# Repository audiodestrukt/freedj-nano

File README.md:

# freedj-nano

A DJ deck for the smallest ESP32s: **one core, no FPU, no PSRAM** (ESP32-C6 first). The
little sibling of [freedj-esp](../freedj-esp), which needs two cores, an FPU and PSRAM (P4,
S3, A1S). The two repos share the deck's vocabulary (`deck::Event`, the DJ2Go map) but not
the engine: everything here is fixed-point and allocation-free in the audio path.

Status (2026-11-10): **runs and plays audio on the XIAO ESP32C6** through a PCM5102A. It
boots, maps the tracks, and plays, cues and keylocks from the serial console at
5 % of the core. The portable core passes its host tests (keylock pitch, speed and level,
click-free transitions, the UI layouts); the firmware builds for three configs.

Why it's built this way, the measurements and the wrong turns: [docs/DESIGN.md](docs/DESIGN.md).

## What's here

| | |
|---|---|
| **Keylock** (`stretch.cpp`) | WSOLA in fixed point, reading straight from memory-mapped PCM, so no input or overlap buffers: two frames at 50 % overlap, a sin² window whose halves sum to exactly 1, coarse-then-fine AMDF search on mono. About 40 bytes of state. 0.5–2× speed; outside that (and while scratching) it's varispeed |
| **Varispeed** | Linear interpolation at a Q16.16 position: any speed, reverse, scratch crawl |
| **Deck** (`deck.cpp`) | CDJ transport (PLAY, CUE with preview), tempo fader and ranges (±6/10/16/50 %), keylock, jog: nudge while playing, scrub while stopped, scratch while touched. Every jump (cue, load, play, stop, engine switch) is a one-block crossfade, so nothing clicks. Lock-free event queue from the control task, seqlock status for the UI |
| **Tracks** (`library.cpp`, `tools/pack_tracks.py`) | A pack of 16-bit PCM plus 10 ms peak tables, flashed into a partition and memory-mapped: loading a track is pointer arithmetic |
| **MIDI** (`midi.cpp`, `dj2go.cpp`) | Byte-stream parser (running status, real-time, SysEx) for DIN/TRS MIDI on a UART, and freedj-esp's DJ2Go map. The C6 has no USB host: a USB controller needs a USB-to-DIN host box, or BLE-MIDI later |
| **Screens** (`gfx.cpp`, `ui.cpp`) | One small drawing interface, a built-in 5×7 font, three layouts by size: 128×32, 128×64, and color 320×240 / 480×320 with touch buttons and drag-to-scratch on the waveform |
| **Firmware** (`firmware/`) | ESP-IDF 5.5, ESP32-C6: I2S to a PCM5102A, EC11 on PCNT, buttons (GPIO or one-pin resistor ladder), pitch pot, MIDI UART, display backends |

### Displays

| Backend | Panels | How |
|---|---|---|
| `display_u8g2.cpp` | SSD1306 128×64 (0.96"), SH1106 128×64 (1.3"), SSD1306 128×32 (0.91") | [u8g2](https://github.com/olikraus/u8g2) as the controller driver and frame buffer, on I2C. Any other u8g2 panel (SSD1309, ST7567, ...) is one more `Setup` line. u8g2 is only the driver: the UI and font are ours, so it could be swapped out |
| `display_tft.cpp` | ILI9341 320×240 (the 2.8" and 3.2"), ST7796 480×320 (the 4"), FT6336 touch | ESP-IDF `esp_lcd` over SPI, no LVGL. No frame buffer: the screen is drawn in 16-row bands into two DMA buffers, and a band is sent only if it changed (hash per band) |

The ST7796 runs on the ILI9341 driver with its own init sequence, because Espressif's ST7796
component doesn't list the C6 as a target.

## Screens

| 128×64 OLED | 2.8" TFT |
|---|---|
|  |  |

Rendered on the host by the tests (`build/tests/out/*.ppm`), from the same code the firmware runs.

## Boards

Pin maps are in `firmware/main/board.h`. **Not checked on hardware yet.**

**Seeed XIAO ESP32C6, with the 3.2" touch TFT** (`xiao_tft`): runs on the bench at 28.5 fps,
17.6 ms per frame at 40 MHz SPI (the A1S manages 7 fps on the same panel: its screen lines are
shared). The screen takes the encoder's pins, so touch does jog and browse: SCK D8, MOSI D10,
CS D3, DC D9, touch SDA D4 / SCL D5; panel RST, LED and CTP_RST to 3V3, VCC to 5V; I2S BCK D1,
LRCK D2, DIN **D6**; ladder D0; MIDI D7.

**Seeed XIAO ESP32C6 with an OLED** (`xiao_oled`, the default): OLED + encoder:

| Pin | Use |
|---|---|
| D1 / D2 / D10 (GPIO 1 / 2 / 18) | I2S BCK / LRCK / DIN to the PCM5102A |
| D4 / D5 (22 / 23) | I2C SDA / SCL: OLED |
| D8 / D9 / D3 (19 / 20 / 21) | EC11 A / B / push |
| D0 (0, ADC) | 4 buttons on a ladder: 10k to 3V3, then PLAY 0R, CUE 2k2, KEY 4k7, LIST 10k to GND |
| D7 (17) | MIDI in (UART1 RX, via an optocoupler) |
| D6 (16) | spare |

**ESP32-C6-DevKitC-1** (`devkit_tft` for the 2.8"/3.2", `devkit_tft4` for the 4"): TFT SCK 6,
MOSI 7, CS 18, DC 19, RST to 3V3; touch and OLED on I2C 22/23; I2S 10/11/21; EC11 3/5,
push on 9 (the BOOT button); PLAY 0, CUE 1, KEY 2; pitch pot on 4; MIDI in on 20.

**PCM5102A** breakout: SCK to GND (no MCLK: its PLL runs off BCK, which is set to 64 fs),
XSMT high, FMT low. Line out only; a headphone amp is a separate board.

## Controls

| | |
|---|---|
| Encoder | Jog: nudge while playing, scrub while stopped |
| KEY + encoder | Tempo (boards without a pot). KEY tap: keylock |
| Push or LIST | Track list. In the list, the encoder browses and push loads |
| PLAY, CUE | As on a CDJ: CUE while playing returns to the cue and pauses; CUE while paused sets the cue and previews while held; PLAY during a preview keeps playing |
| Touch (TFT) | CUE / PLAY / KEY / LIST buttons; drag the waveform to scratch |
| MIDI | The DJ2Go map: either deck's controls drive the one deck |
| Controller on the computer | freedj-esp's `tools/midi_bridge.py --port /dev/ttyACM0` forwards a USB controller (the DJ2Go) over the serial port: 0x01 + a USB-MIDI packet, decoded with the DJ2Go map |
| Serial console | Over the USB port, for the bench: `p` play, `c` cue (tap), `k` keylock, `+` / `-` tempo 1 %, `0` tempo 0, `r` range, `n` / `b` next / previous track, `j` / `J` jog, `l` list, `?` help. Keys sent while it boots are lost (opening the port resets the C6) |

## Build

```sh
tools/build.sh                          # all firmware configs (Docker, ESP-IDF 5.5) + host tests
tools/build.sh devkit_tft               # one config
cmake -S tests -B build/tests && cmake --build build/tests && (cd build/tests && ./nano_tests)
```

Host tests write listening files (`out/keylock_080.wav`, `keylock_125.wav`, `deck_session.wav`)
and screenshots of every layout.

## Flash

```sh
cd firmware/build_xiao_oled && esptool --chip esp32c6 -b 460800 write-flash @flash_args
tools/pack_tracks.py music/*.mp3 -o tracks.bin     # 22.05 kHz mono; --stereo, --rate 32000
esptool --chip esp32c6 write-flash 0x180000 tracks.bin
```

The `tracks` partition is 2.5 MB on a 4 MB board: about 60 s of 22.05 kHz mono. Fine for
bring-up; storage is the first thing to grow (see the roadmap).

## Budget

| | xiao_oled | devkit_tft |
|---|---|---|
| App image | 269 KB (82 % of the partition free) | 312 KB |
| Static RAM (DIRAM) | 69 KB of 452 KB | 79 KB |
| Audio CPU, 22.05 kHz mono | stopped 0.5 %, playing 1.4 %, **keylock 5.0 %** (XIAO, 160 MHz) | |
| Audio CPU, 44.1 kHz stereo | playing 3.1 %, **keylock 16.4 %, worst block 34 % of its deadline, 0 dropouts** (with the TFT at ~43 fps) | |
| Free heap while playing | 424 KB | |

The firmware prints a budget line every 2 s: audio % of the core (and which engine), UI ms per
frame, free heap.

## Roadmap

1. **Bench bring-up** on the XIAO: audio out, the budget line, encoder and ladder.
2. **More music:** stream from microSD instead of flash (needs a small read-ahead cache for
   the keylock's random access), or IMA ADPCM in the pack (4:1, block-wise so it stays
   seekable).
3. **BLE-MIDI**, since the C6 has no USB host.
4. **New chips** ([docs/TARGETS.md](docs/TARGETS.md)): the **RP2350** as the second real
   target (two cores, memory-mapped flash, PIO I2S, USB host for rekordbox sticks), and the
   **CH32V003** (10 cents, 2 KB RAM, PWM audio) as a how-small-can-it-go experiment
   ([the 10-cent deck plan](docs/DECK10C.md)). First
   step: cross-compile the engine and count cycles per sample.
5. Beetle ESP32-C6 pin map; the C3/H2.

## License

GPL-3.0-or-later, as freedj-esp. `deck_event` and `dj2go` are copied from freedj-esp
(2026-11-08). u8g2 is BSD-2-Clause; the Helvetica bitmap fonts in `fonts.cpp` are Adobe / DEC under the X11
license; the ST7796 init sequence is from Espressif's
esp_lcd_st7796 (Apache-2.0).

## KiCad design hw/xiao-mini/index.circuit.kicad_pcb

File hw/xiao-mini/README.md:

# XIAO mini player (carrier board)

A 72 x 46 mm, 2-layer carrier for a socketed **Seeed XIAO ESP32-C6**. It wires everything the
C6 firmware already expects (`firmware/main/board.h`, `CONFIG_NANO_BOARD_XIAO_C6`, OLED
layout), so it runs today's C6 build unchanged: 16-bit audio through a PCM5102A DAC.

| Block | Parts | XIAO pins |
|---|---|---|
| DAC | PCM5102A (hardware mode: SCK, FMT, FLT, DEMP to GND, XSMT pulled up), 470 R + 2.2 nF out | D1 BCK, D2 WS, D10 DOUT |
| Out | 3.5 mm stereo jack, left edge. **Line level** (into a mixer or powered speakers); the PCM5102A wants >= 1 kOhm, so headphones will be quiet and distort when loud | |
| Screen | 4-pin header for a 0.96" / 1.3" SSD1306/SH1106 I2C module: GND VCC SCL SDA | D4 SDA, D5 SCL |
| Jog / browse | EC11 (Bourns PEC11R) with push, 10k pull-ups | D8 A, D9 B, D3 push |
| Buttons | PLAY, CUE, KEY, LIST on one ADC pin: 10k pull-up, 0 / 2k2 / 4k7 / 10k to GND (the firmware's `LADDER_MV`) | D0 |
| MIDI in | 3-pin header GND RX 3V3, for the bridge's UART | D7 |
| Battery | JST-PH LiPo socket, right edge, plus two pads beside it: wire them to the BAT pads under the XIAO (it has the charger) | |
| Spare | | D6 |

USB-C (the XIAO's) leaves the top edge. Four M2 holes in the corners.

## State

Routed and checked: 0 shorts, 0 open nets, KiCad DRC clean under JLCPCB rules, DFM (hole
spacing, via sizes) clean, no floating pads. `fab/` has Gerbers, drill, CPL and BOMs for JLCPCB
(assembled: DAC, passives, jack, JST, EC11, buttons) and PCBWay. Not built yet.

**Check before ordering:**
- **Jack pinout.** No datasheet drawing for the PJ-325C5-G was found. The board assumes pin 1
  sleeve, 2 tip (L), 3 ring (R) (`JACK_PIN` in `index.circuit.tsx`). Check the part (a
  multimeter on a sample, or the drawing) or swap in a jack you know.
- **OLED header order.** GND VCC SCL SDA is the common one, but some modules are VCC GND.
- **R2 / R3 (470 R)** have no LCSC number yet (in the hand-solder list): pick one at order time.
- **XIAO row spacing** (15.24 mm) and the JST's polarity against your batteries.

## Rebuild

```
npm ci                                   # tscircuit, pinned by package-lock.json
bash scripts/route2.sh                   # export, outline gate, GND pour, route (Freerouting + srj), DRC
bash scripts/make_fab.sh index.circuit.kicad_pcb freedj-nano-xiao-mini both
```

The source of truth is `index.circuit.tsx` (placement in code); `index.circuit.kicad_pcb` is the
routed result. Parts: `imports/` (JLC footprints), `lib/Xiao.tsx` (the socket),
`lib/GndVia.tsx` (stitching vias for the DAC's tie-low pins, as parts so the router keeps them).
Scripts are the pcb-layout skill's.

## Other XIAOs

The S3, C3 and RP2040/RP2350 XIAOs have the same pinout and fit the same socket; the firmware
needs a pin map for each (the S3 one would follow freedj-esp's S3 port).

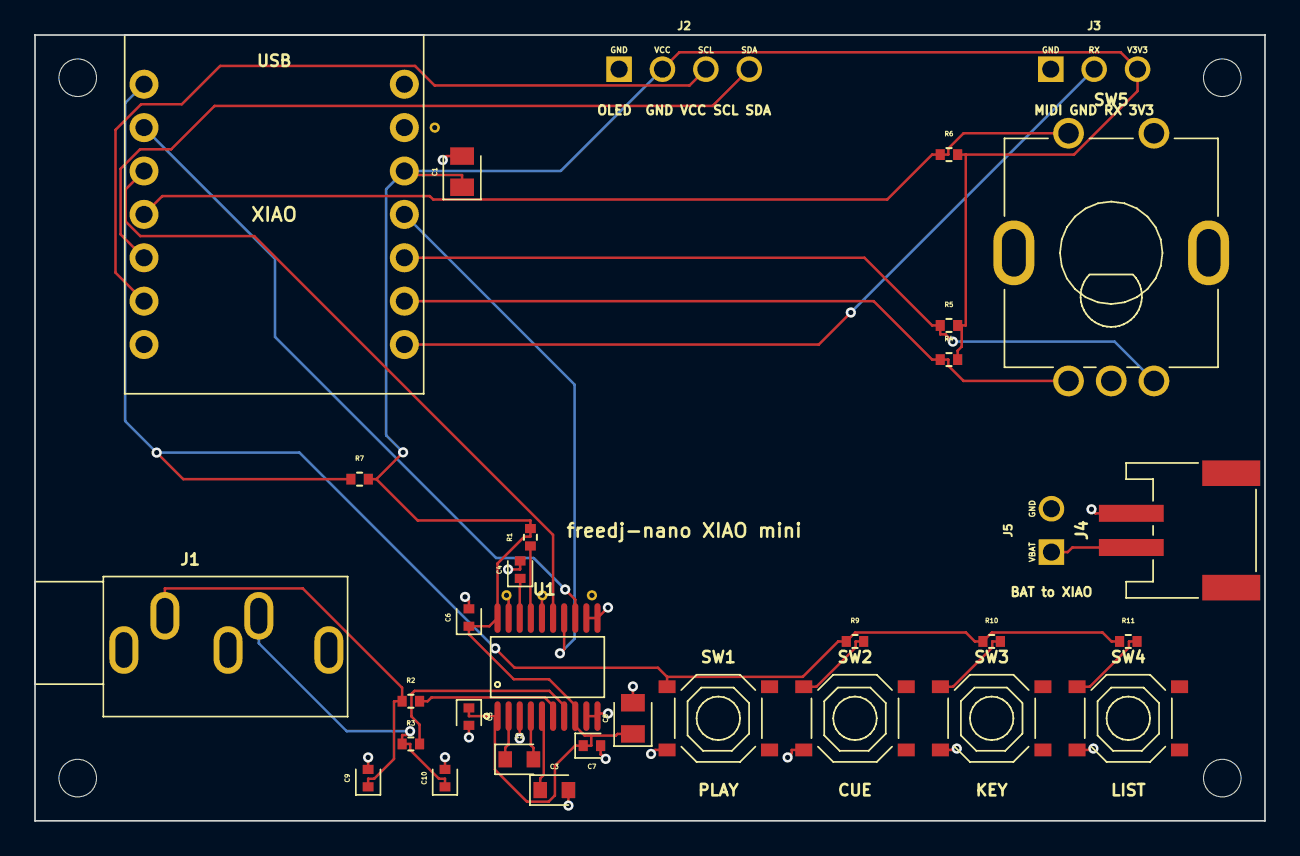
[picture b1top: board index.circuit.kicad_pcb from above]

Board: 2 copper layers, 72.0 x 46.0 mm, 36 parts (0 on the bottom side), 25 nets.

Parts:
C1, C8: 10uF; capacitor_0805
C2, C3: 2.2uF; capacitor_0603
C4: 1uF; capacitor_0402
C5, C6, C7: 100nF; capacitor_0402
C9, C10: 2.2nF; capacitor_0402
J1: PJ_325C5_G
J2: J2; pin_header_pinrow4
J3: J3; pin_header_pinrow3
J4: S2B_PH_SM4_TB_LF__SN_; S2B_PH_SM4_TB_LF_SN
J5: J5; pin_header_pinrow2
R1, R4, R5, R6, R7, R11: 10kΩ; resistor_res0402
R2, R3: 470Ω; resistor_res0402
R9: 2.2kΩ; resistor_res0402
R10: 4.7kΩ; resistor_res0402
SW1, SW2, SW3, SW4: TS_1187A_B_A_B
SW5: PEC11R_4015F_S0024
U1: PCM5102APWR
U2: Seeed_XIAO_socketed
V1, V2, V3, V4: via

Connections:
BCK: U1.13, U2.2
C2.pin1 to U1.CAPP: C2.1, U1.2
C2.pin2 to U1.CAPM: C2.2, U1.4
C3.pin1 to U1.VNEG: C3.1, U1.5
C4.pin1 to U1.LDOO: C4.1, U1.18
DIN: U1.14, U2.11
ENC_A: R4.1, SW5.3, U2.13
ENC_B: R5.1, SW5.5, U2.12
ENC_SW: R6.1, SW5.1, U2.4
GND: C1.2, C3.2, C4.2, C5.2, C6.2, C7.2, C8.2, C9.2, C10.2, J1.1, J2.1, J3.1, J4.2, J5.2, SW1.3, SW2.3, SW3.3, SW4.3, SW5.2, SW5.4, SW5.6, SW5.7, U1.3, U1.9, U1.10, U1.11, U1.12, U1.16, U1.19, U2.9, V1.1, V2.1, V3.1, V4.1
JL: C9.1, J1.2, R2.1
JR: C10.1, J1.3, R3.1
LADDER: R7.1, R9.1, R10.1, R11.1, SW1.1, U2.1
LRCK: U1.15, U2.3
MIDI_RX: J3.2, U2.14
R1.pin1 to U1.XSMT: R1.1, U1.17
R2.pin2 to U1.OUTL: R2.2, U1.6
R3.pin2 to U1.OUTR: R3.2, U1.7
R9.pin2 to SW2.A: R9.2, SW2.1
R10.pin2 to SW3.A: R10.2, SW3.1
R11.pin2 to SW4.A: R11.2, SW4.1
SCL: J2.3, U2.6
SDA: J2.4, U2.5
V3V3: C1.1, C5.1, C6.1, C7.1, C8.1, J2.2, J3.3, R1.2, R4.2, R5.2, R6.2, R7.2, U1.1, U1.8, U1.20, U2.10
VBAT: J4.1, J5.1

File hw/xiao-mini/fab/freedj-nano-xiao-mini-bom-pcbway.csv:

Item#,Designator,Qty,Comment,Footprint,Manufacturer Part Number,Manufacturer,LCSC Part No
1,"C1,C8",2,10uF,capacitor_0805,CL21A106KAYNNNE,Samsung Electro-Mechanics,C15850
2,"C10,C9",2,2.2nF,capacitor_0402,CC0402KRX7R9BB222,YAGEO,C106861
3,"C2,C3",2,2.2uF,capacitor_0603,CL10A225KO8NNNC,Samsung Electro-Mechanics,C23630
4,C4,1,1uF,capacitor_0402,CL05A105KA5NQNC,Samsung Electro-Mechanics,C52923
5,"C5,C6,C7",3,100nF,capacitor_0402,CL05B104KO5NNNC,Samsung Electro-Mechanics,C1525
6,J1,1,PJ_325C5_G,PJ_325C5_G,PJ_325C5_G,,C692438
7,J4,1,S2B_PH_SM4_TB_LF__SN_,S2B_PH_SM4_TB_LF_SN,S2B_PH_SM4_TB_LF__SN_,,C295747
8,R10,1,4.7k,resistor_res0402,ERJ2RKF4701X,Panasonic,C400631
9,"R1,R11,R4,R5,R6,R7",6,10k,resistor_res0402,0402WGF1002TCE,UNI-ROYAL(Uniroyal Elec),C25744
10,R9,1,2.2k,resistor_res0402,0402WGF2201TCE,UNI-ROYAL(Uniroyal Elec),C25879
11,SW5,1,PEC11R_4015F_S0024,PEC11R_4015F_S0024,PEC11R_4015F_S0024,,C143789
12,"SW1,SW2,SW3,SW4",4,TS_1187A_B_A_B,TS_1187A_B_A_B,TS_1187A_B_A_B,,C318884
13,U1,1,PCM5102APWR,PCM5102APWR,PCM5102APWR,,C107671

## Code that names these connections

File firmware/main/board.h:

// SPDX-FileCopyrightText: 2026 Dan Newcome
// SPDX-License-Identifier: GPL-3.0-or-later
#pragma once
// Pin maps. Not checked on hardware yet: confirm against the board's pinout
// before wiring. C6 pins to avoid: 8, 9, 15 (strapping; 9 is BOOT, fine as an
// input after boot), 12/13 (USB), 24-30 (flash).

#include "driver/gpio.h"
#include "sdkconfig.h"

namespace board {

constexpr gpio_num_t NC = GPIO_NUM_NC;

#if CONFIG_NANO_BOARD_XIAO_C6
// Seeed XIAO ESP32C6: D0=0 D1=1 D2=2 D3=21 D4=22 D5=23 D6=16 D7=17 D8=19 D9=20 D10=18.
// Eleven pins, so the four buttons share one ADC pin (resistor ladder). Two layouts:
// an I2C OLED + EC11, or an SPI TFT + touch that takes the encoder's pins (touch
// does jog and browse) and moves I2S DOUT to D6.
constexpr const char* NAME = "XIAO ESP32C6";
constexpr gpio_num_t I2C_SDA = GPIO_NUM_22, I2C_SCL = GPIO_NUM_23;                         // D4, D5: OLED or touch
#if CONFIG_NANO_DISPLAY_TFT
constexpr gpio_num_t I2S_BCK = GPIO_NUM_1,  I2S_WS = GPIO_NUM_2, I2S_DOUT = GPIO_NUM_16;   // D1, D2, D6 -> PCM5102A
constexpr gpio_num_t ENC_A = GPIO_NUM_NC,   ENC_B = GPIO_NUM_NC, ENC_PUSH = GPIO_NUM_NC;
// SCK D8, MOSI D10, CS D3, DC D9. Panel RST, LED and CTP_RST to 3V3; SDO and CTP_INT unused.
constexpr gpio_num_t TFT_SCK = GPIO_NUM_19, TFT_MOSI = GPIO_NUM_18, TFT_CS = GPIO_NUM_21, TFT_DC = GPIO_NUM_20;
constexpr gpio_num_t TFT_RST = GPIO_NUM_NC;
#else
constexpr gpio_num_t I2S_BCK = GPIO_NUM_1,  I2S_WS = GPIO_NUM_2, I2S_DOUT = GPIO_NUM_18;   // D1, D2, D10 -> PCM5102A
constexpr gpio_num_t ENC_A = GPIO_NUM_19,   ENC_B = GPIO_NUM_20, ENC_PUSH = GPIO_NUM_21;   // D8, D9, D3: EC11
constexpr gpio_num_t TFT_SCK = GPIO_NUM_NC, TFT_MOSI = GPIO_NUM_NC, TFT_CS = GPIO_NUM_NC, TFT_DC = GPIO_NUM_NC, TFT_RST = GPIO_NUM_NC;
#endif
constexpr gpio_num_t MIDI_RX = GPIO_NUM_17;                                                 // D7
// Button ladder on D0 (ADC1 ch 0): 10k pull-up to 3V3, each button to GND
// through its resistor. Nominal mV with nothing pressed: 3300.
constexpr gpio_num_t LADDER = GPIO_NUM_0;
constexpr int LADDER_CH = 0;
// PLAY 0R (0 mV), CUE 2k2 (595), KEY 4k7 (1055), LIST 10k (1650)
constexpr int LADDER_MV[4] = {0, 595, 1055, 1650};
constexpr gpio_num_t BTN_PLAY = NC, BTN_CUE = NC, BTN_KEY = NC, BTN_LIST = NC;
constexpr gpio_num_t POT = NC; constexpr int POT_CH = -1;

#elif CONFIG_NANO_BOARD_DEVKIT_C6
// ESP32-C6-DevKitC-1. TFT on the SPI2 IOMUX pins (6, 7) for the full clock.
constexpr const char* NAME = "ESP32-C6-DevKitC-1";
constexpr gpio_num_t I2S_BCK = GPIO_NUM_10, I2S_WS = GPIO_NUM_11, I2S_DOUT = GPIO_NUM_21;
constexpr gpio_num_t I2C_SDA = GPIO_NUM_22, I2C_SCL = GPIO_NUM_23;                         // OLED or touch
constexpr gpio_num_t ENC_A = GPIO_NUM_3,    ENC_B = GPIO_NUM_5,  ENC_PUSH = GPIO_NUM_9;    // push = BOOT button too
constexpr gpio_num_t MIDI_RX = GPIO_NUM_20;
constexpr gpio_num_t BTN_PLAY = GPIO_NUM_0, BTN_CUE = GPIO_NUM_1, BTN_KEY = GPIO_NUM_2, BTN_LIST = NC;
constexpr gpio_num_t LADDER = NC; constexpr int LADDER_CH = -1;
constexpr int LADDER_MV[4] = {0, 0, 0, 0};
constexpr gpio_num_t POT = GPIO_NUM_4; constexpr int POT_CH = 4;                           // ADC1 ch 4
constexpr gpio_num_t TFT_SCK = GPIO_NUM_6, TFT_MOSI = GPIO_NUM_7, TFT_CS = GPIO_NUM_18, TFT_DC = GPIO_NUM_19;
constexpr gpio_num_t TFT_RST = NC;   // tie the panel's RST to 3V3: the driver sends a software reset
#endif

} // namespace board
